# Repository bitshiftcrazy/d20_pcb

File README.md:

# d20 PCB

A handheld electronic D20 built as a DnD-themed PCB project.

The board uses an ATtiny84, charlieplexed LEDs, capacitive touch input,
custom animations, EEPROM-backed "attunement", and hidden easter eggs to
turn a PCB into a slightly magical-feeling tabletop artifact. For dice
rolls, dramatic failures, heroic last minutes, and other shenanigans ;)

## Features

- Electronic D20 with animated rolls
- Capacitive touch dice rolling
- Character-specific animation variants
- EEPROM-backed attunement system
- Hidden easter eggs and secret modes
- Fully open hardware and open source firmware
- Mildly questionable choices and amounts of whimsy

## Usage

### Power On

Turn on the board using the slide switch on the right side.

The board spends most of its existence asleep, patiently waiting for
an adventurer to wake it.

### Wake Up

Press the push button on the back once to wake the board.

The LEDs should come to life shortly afterwards.

### Rolling

Rolls can be triggered either by:

- pressing the push button
- briefly touching and releasing the `20` touch pad

The pushbutton has the power to interrupt rolls, should fate require it.

The touch sensor is intentionally configured conservatively to avoid
accidental triggers and random table wizardry (everyone who's seen an actual Pen and Paper table will know why).

Touch works best while holding the board in your hand and touching the
pad between thumb and index finger (there has been some discussion about
this...).

Touch sensitivity can be adjusted in `firmware/src/touch.c`.

See the firmware README for more information.

## Attunement

The board features a small "attunement" system inspired by magical items
in tabletop RPGs.

On first activation, the firmware stores a tiny hardware-specific value in
EEPROM based on touch pad readings. This subtly affects animation timing
and behavior, making each board feel ever so slightly different.

## Repository Structure

```text
hardware/   KiCad PCB design, manufacturing files and artwork
firmware/   ATtiny84 firmware and test infrastructure
docs/       Images and documentation assets
```

Detailed instructions are available in:

- [hardware/README.md](hardware/README.md)
- [firmware/README.md](firmware/README.md)

## Easter Eggs

The firmware contains several hidden interactions and modes and, yeah, an attitude.

Some are obvious.
Some are less obvious.

Some still haven't been found yet.

## Project Background

This project originally started as a handmade DnD-themed gift for my
players, with far more LEDs, firmware, and suspicious EEPROM usage than originally planned.
And now it's an open hardware project.

There's customisation for both the players and the campaign hidden
throughout the project because of how it came to be.
The different character's animation can be interpreted as flavour and compiled in to your liking.

## Further Reading

- Project blog post: https://missmolerat.com/posts/d20_pcb/
- Hackaday: https://hackaday.com/2026/05/25/slightly-sentient-d20-might-subtly-shift-your-rolls/

## Licenses

- Hardware: CERN Open Hardware License
- Firmware: GPL-3.0-only

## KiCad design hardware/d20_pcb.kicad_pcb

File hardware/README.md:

# d20 PCB – Hardware

This directory contains the KiCad design files, artwork, and
manufacturing outputs for the d20 PCB.

The board is a small ATtiny-based electronic die with 20 LEDs arranged
around the edge of a d20-shaped PCB. A capacitive touch pad triggers a
roll animation and displays a random result.

## Hardware Overview

Main components:

- ATtiny84 microcontroller
- 20 LEDs arranged in a ring (charlieplexed)
- Capacitive touch pad for input
- Coin cell battery holder
- Push button (optional backup input)

## Directory Structure

```text
d20_pcb.kicad_pro
d20_pcb.kicad_sch
d20_pcb.kicad_pcb
```

KiCad project files.

```text
artwork/
```

SVG artwork used for silkscreen and copper layers.

```text
libraries/
```

Project-local KiCad symbol and footprint libraries.

```text
fabrication/
```

Generated manufacturing files:

- `gerbers/`
- `drill/`
- `bom/`
- `pickplace/`

```text
fabrication/jlcpcb/
```

Vendor-specific BOM and placement files for JLCPCB assembly.

### JLCPCB Component Substitutions

Component availability at JLCPCB/LCSC changes over time. During a 2026
JLCPCB assembly order, the following substitutions were proposed for the
v3 BOM:

| Designator | Original value / function | Substitute | Notes |
| --- | --- | --- | --- |
| C2 | 10 µF | C7472949 — HGC0402R5106M100NTEJ | 10 µF, 10 V, 0402 MLCC. Original C6119763 was out of stock. |
| R1–R5 | 150 Ω | C2909321 — FRC0402F1500TS | 150 Ω, 1%, 0402 |
| R7–R8 | 10 kΩ | C723366 — RT0402FRE0710KL | 10 kΩ, 1%, 0402 thin-film resistor, YAGEO |
| J1 | ISP header | C48641755 — HX PM2.54-1x6P | SMD female 1×6 header with staggered pins. The original BOM entry had no LCSC part number. |
| J2 and G* | — | DNP | No physical components fitted. |

The suggested C2 replacement is a ceramic MLCC rather than the capacitor
specified in the original BOM. Component substitutions should always be
reviewed before ordering, since stock and JLCPCB/LCSC part assignments
can change.

Thanks to [@dmaglio](https://github.com/dmaglio) for reporting these
substitutions in [issue #1](https://github.com/bitshiftcrazy/d20_pcb/issues/1).

## KiCad Project

The board is designed using KiCad.

Main files:

- `d20_pcb.kicad_pro` – project file
- `d20_pcb.kicad_sch` – schematic
- `d20_pcb.kicad_pcb` – PCB layout

The project uses local libraries located in:

```text
libraries/
```

## Artwork

Silkscreen and copper artwork is stored as SVG files in:

```text
artwork/
```

These files were used to create decorative PCB elements such as:

- board outline
- line art
- map on the back
- decorative stars and moons

## Manufacturing

All required manufacturing outputs are located in:

```text
fabrication/
```

To manufacture the board:

1. Upload files from `fabrication/gerbers/` to a PCB manufacturer.
2. Use files from `fabrication/drill/` for drilling information.
3. Use the BOM and pick-and-place files for assembly.

Note: the more detailed assembly BOM with parts and values is located in:

```text
fabrication/jlcpcb/
```

Alternatively:

The files in `fabrication/releases/` contain the currently tested and
successfully manufactured board revision.

If you modify the KiCad source files, you should regenerate and review
all fabrication outputs (Gerbers, drill files, BOM, and pick-and-place
files) before ordering boards.

Even small PCB edits can invalidate previously generated fabrication
files.

If you are new to PCB manufacturing, it is recommended to use the tested
release files directly instead of generating new Gerbers yourself.

## Regenerating Fabrication Files

Manufacturing files can be regenerated from KiCad:

```text
PCB Editor → Fabrication Outputs
```

## Assembly

### Supplies

* soldering iron (alternatively: heat plate or hot air)
* solder (alternatively: solder paste)
* flux
* fume extractor or a well-ventilated space

### Parts

Many of the parts are influenced by what I had at home at the time.

Quite a few can be swapped for whatever matches the footprint. I found that old TV remotes are wonderful donors for slide switches and push buttons, for example. At least that's where I got these components from.

* 20 x SMD LEDs (0603)
* 1 x 0.1 µF capacitor (0402)
* 1 x 10 µF capacitor (0402)
* 1 x 10 nF capacitor (0402)
* 5 x 150 Ω resistors (0402)
* 2 x 10 kΩ resistors (0402)
* 1 x 1 MΩ resistor (0402)
* 1 x Keystone 1060TR battery holder
* 1 x CR2032 coin cell battery
* 1 x ATtiny84-20P Microchip ATTINY84A-SSF
* 1 x SPDT slide switch (see footprint; many ~8 mm SMD slide switches will fit, AliExpress has quite a few)
* 1 x push button (same here; 3.4 x 3.4 mm SMD push buttons often work)

I'd really love to point towards specific components for the slide switch or push button. But apart from sourcing the part via JLCPCB assembly or scavenging it, I have none.

Really, have faith: as long as you manage to connect the footprint pads with the part pins somehow, a lot of switches will work here (source: trust me bro).

### Soldering

## Colour Suggestions

The board was intentionally designed with colourful solder masks and
ENIG finishes in mind.

~~I'd really love to see a pink board!~~

Mission accomplished :D

For comparison, here are the original render concepts:

## License

This hardware design is licensed under the CERN Open Hardware Licence
Version 2 – Strongly Reciprocal (CERN-OHL-S v2).

You may manufacture, modify and sell products based on this design,
provided that any modifications to the design files are released under
the same license.

The full license text is available in the LICENSE file.

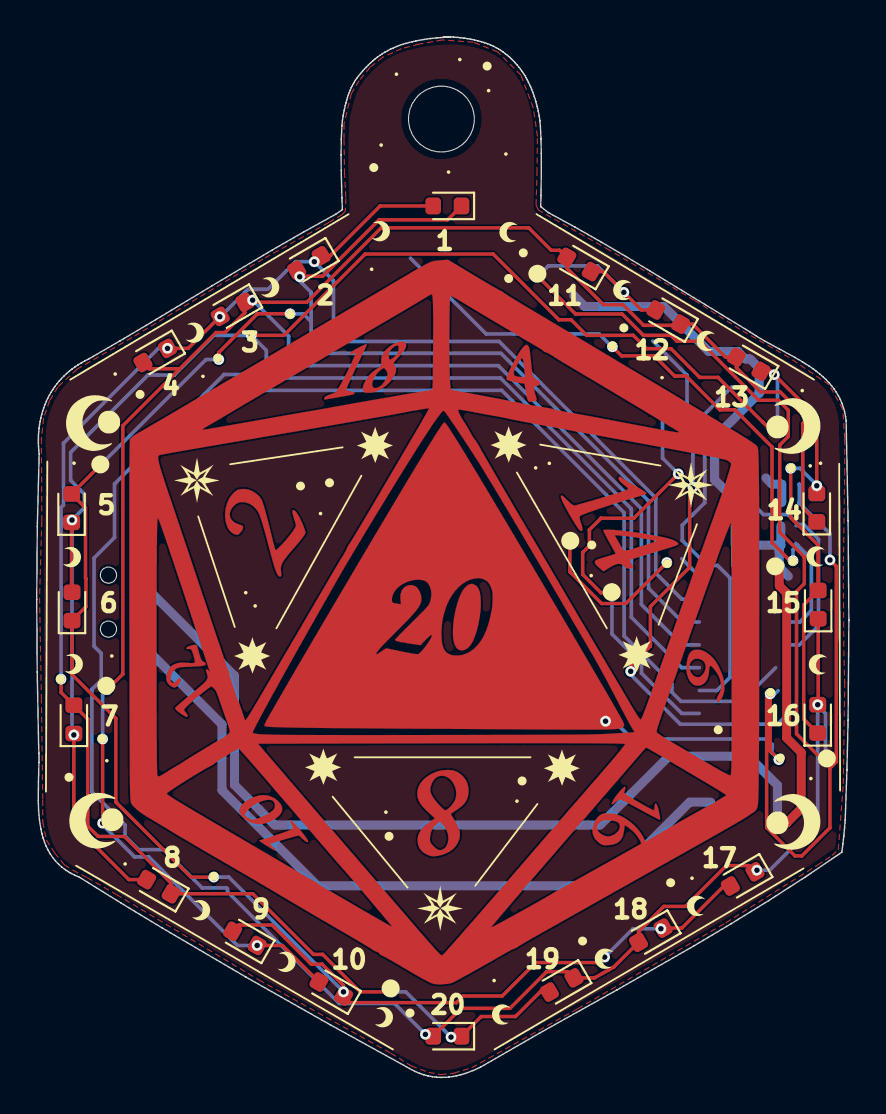
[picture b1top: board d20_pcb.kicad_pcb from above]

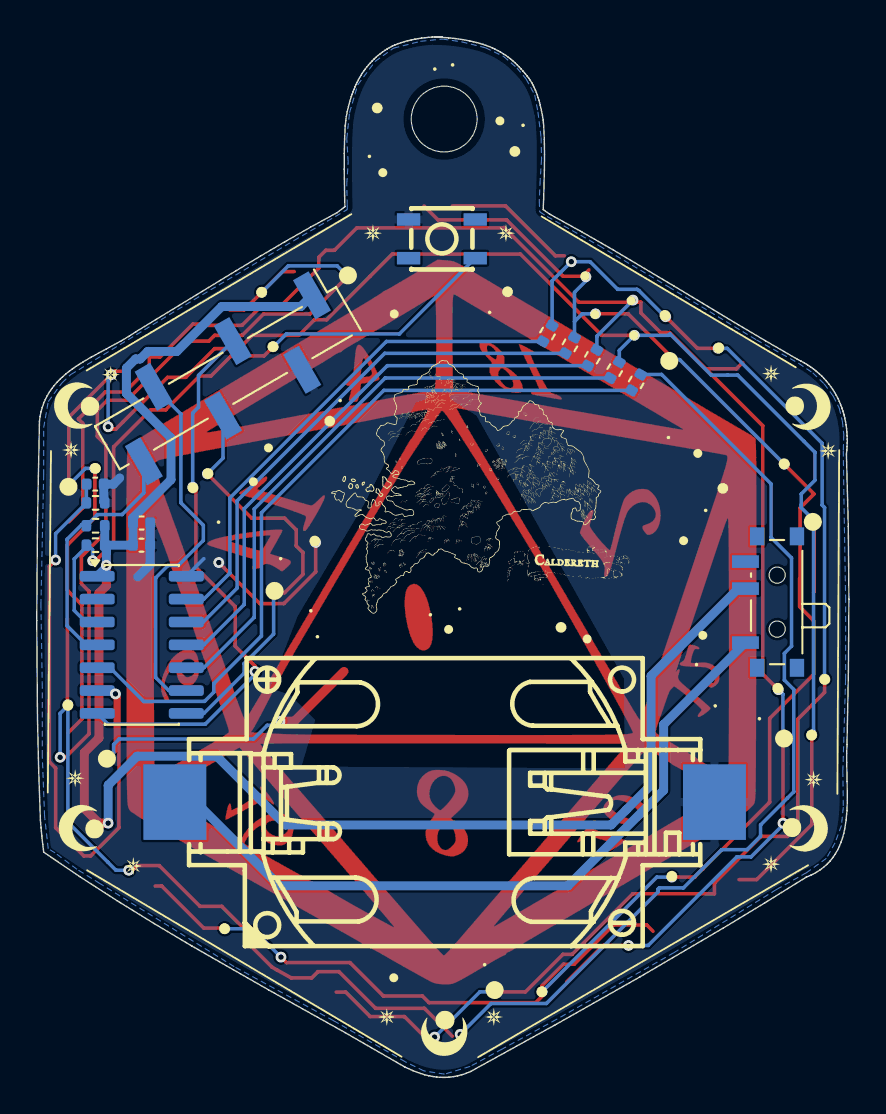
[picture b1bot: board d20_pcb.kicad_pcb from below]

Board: 2 copper layers, 45.1 x 57.8 mm, 37 parts (16 on the bottom side), 19 nets.

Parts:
BT1: Battery_Cell; d20_battery
C1(Ceramic)1: 0.1uF; C_0402_1005Metric
C2(Electrolytic)1: 10uF; C_0402_1005Metric
C3: 10nF; C_0402_1005Metric
D1, D2, D3, D4, D5, D6, D7, D8, D9, D10, D11, D12, D13, D14, D15, D16, D17, D18, D19, D20: LED; LED_0603_1608Metric
J1: Conn_01x06_Socket; PinHeader_1x06_P2.54mm_Vertical_SMD_Pin1Left
J2: Conn_01x01_Pin; d20_touchpad
R1, R2, R3, R4, R5: 150 Ohm; R_0402_1005Metric
R6: 1MOhm; R_0402_1005Metric
R7, R8: 10kOhm; R_0402_1005Metric
SW1: SW_SPST; SW_SPDT_PCM12
SW2: SW_Push; d20_pushbutton
U1: ATtiny84-20P; SOIC-14_3.9x8.7mm_P1.27mm

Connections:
A: R1.1, U1.13 (AREF/PA0)
B: R2.1, U1.12 (PA1)
C: R3.1, U1.11 (PA2)
D: R4.1, U1.10 (PA3)
E: R5.1, U1.5 (PB2)
GND: BT1.2 (-), C1(Ceramic)1.2, C2(Electrolytic)1.2, C3.2, J1.2, R6.2, SW2.4, U1.14 (GND)
MISO: J1.4, U1.8 (PA5)
MOSI: J1.3, U1.7 (PA6)
unnamed: BT1.1 (+), SW1.1 (A)
unnamed: D1.2 (A), D2.1 (K), D3.2 (A), D4.1 (K), D7.2 (A), D8.1 (K), D19.2 (A), D20.1 (K), R1.2
unnamed: D1.1 (K), D2.2 (A), D5.2 (A), D6.1 (K), D9.2 (A), D10.1 (K), D17.2 (A), D18.1 (K), R2.2
unnamed: D3.1 (K), D4.2 (A), D9.1 (K), D10.2 (A), D11.2 (A), D12.1 (K), D13.2 (A), D14.1 (K), R3.2
unnamed: D11.1 (K), D12.2 (A), D15.1 (K), D16.2 (A), D17.1 (K), D18.2 (A), D19.1 (K), D20.2 (A), R5.2
unnamed: D5.1 (K), D6.2 (A), D7.1 (K), D8.2 (A), D13.1 (K), D14.2 (A), D15.2 (A), D16.1 (K), R4.2
PAD: C3.1, J2.1 (Pin_1_1), R6.1, U1.6 (PA7)
PB: R7.2, SW2.1, U1.3 (XTAL2/PB1)
RST: J1.6, R8.2, U1.4 (~RESET/PB3)
SCK: J1.5, U1.9 (PA4)
VCC: C1(Ceramic)1.1, C2(Electrolytic)1.1, J1.1, R7.1, R8.1, SW1.2 (B), U1.1 (VCC)

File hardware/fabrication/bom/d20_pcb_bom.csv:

"Id";"Designator";"Footprint";"Quantity";"Designation";"Supplier and ref";
1;"D7,D10,D6,D19,D4,D20,D18,D1,D12,D16,D13,D5,D15,D9,D3,D17,D14,D11,D8,D2";"LED_0603_1608Metric";20;"LED";;;
2;"J2";"d20_touchpad";1;"Conn_01x01_Pin";;;
3;"G***";"d20_line_art";1;"d20_line_art";;;
4;"R8,R7";"R_0402_1005Metric";2;"10kOhm";;;
5;"R6";"R_0402_1005Metric";1;"1MOhm";;;
6;"J1";"PinHeader_1x06_P2.54mm_Vertical_SMD_Pin1Left";1;"Conn_01x06_Socket";;;
7;"U1";"SOIC-14_3.9x8.7mm_P1.27mm";1;"ATtiny84-20P";;;
8;"R2,R3,R1,R4,R5";"R_0402_1005Metric";5;"150 Ohm";;;
9;"C2(Electrolytic)1";"C_0402_1005Metric";1;"10uF";;;
10;"SW2";"d20_pushbutton";1;"SW_Push";;;
11;"C3";"C_0402_1005Metric";1;"10nF";;;
12;"BT1";"d20_battery";1;"Battery_Cell";;;
13;"SW1";"SW_SPDT_PCM12";1;"SW_SPST";;;
14;"C1(Ceramic)1";"C_0402_1005Metric";1;"0.1uF";;;

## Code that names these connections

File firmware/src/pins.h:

/*
 * SPDX-License-Identifier: GPL-3.0-only
 *
 * Copyright (C) 2025 miss.molerat <bitshiftcrazy@posteo.de>
 */

#ifndef PINS_H
#define PINS_H

#include <avr/io.h>

/*
 * ATtiny84 pin mapping for the d20 PCB
 *
 *                    ATtiny84
 *               +-----------------+
 *         VCC --| 1            14 |-- GND
 *   NC / PB0  --| 2            13 |-- PA0 / A
 * BUTTON / PB1 -| 3            12 |-- PA1 / B
 * RESET / PB3 --| 4            11 |-- PA2 / C
 *      E / PB2 -| 5            10 |-- PA3 / D
 *   PAD / PA7 --| 6             9 |-- PA4 / SCK
 *   MOSI / PA6 -| 7             8 |-- PA5 / MISO
 *               +-----------------+
 *
 * Charlieplex lines:
 *   A -> PA0
 *   B -> PA1
 *   C -> PA2
 *   D -> PA3
 *   E -> PB2
 *
 * Other signals:
 *   BUTTON -> PB1
 *   TOUCH  -> PA7 (ADC7)
 */

/* ------------------------------------------------------------------------- */
/* Charlieplex LED driver pins                                               */
/* ------------------------------------------------------------------------- */

#define LED_A_PORT    PORTA
#define LED_A_DDR     DDRA
#define LED_A_PIN     PA0

#define LED_B_PORT    PORTA
#define LED_B_DDR     DDRA
#define LED_B_PIN     PA1

#define LED_C_PORT    PORTA
#define LED_C_DDR     DDRA
#define LED_C_PIN     PA2

#define LED_D_PORT    PORTA
#define LED_D_DDR     DDRA
#define LED_D_PIN     PA3

#define LED_E_PORT    PORTB
#define LED_E_DDR     DDRB
#define LED_E_PIN     PB2

/* ------------------------------------------------------------------------- */
/* Button input                                                              */
/* ------------------------------------------------------------------------- */

#define BUTTON_PORT   PORTB
#define BUTTON_DDR    DDRB
#define BUTTON_PINREG PINB
#define BUTTON_BIT    PB1

/* ------------------------------------------------------------------------- */
/* Capacitive touch pad                                                      */
/* ------------------------------------------------------------------------- */

#define TOUCH_PORT    PORTA
#define TOUCH_DDR     DDRA
#define TOUCH_PINREG  PINA
#define TOUCH_BIT     PA7

/* ADC channel for touch pad */
#define TOUCH_ADC_CHANNEL 7

#endif /* PINS_H */

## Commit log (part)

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2026-03-09 Initial open hardware release of the d20 PCB design
2026-04-06 HW: move touchpad to analog pin to get rid of firmware hack
2026-04-06 HW: resize caldereth map footprint
2026-04-06 HW: add hw-devel README
2026-05-06 HW: add fabrication output for v3
2026-05-06 HW: add d20v3 pcb
2026-05-06 HW: Add d20v3
    Changes:
    - move touchpad to analog pin
    - resize map artwork
2026-05-06 FW: add initial d20 firmware
